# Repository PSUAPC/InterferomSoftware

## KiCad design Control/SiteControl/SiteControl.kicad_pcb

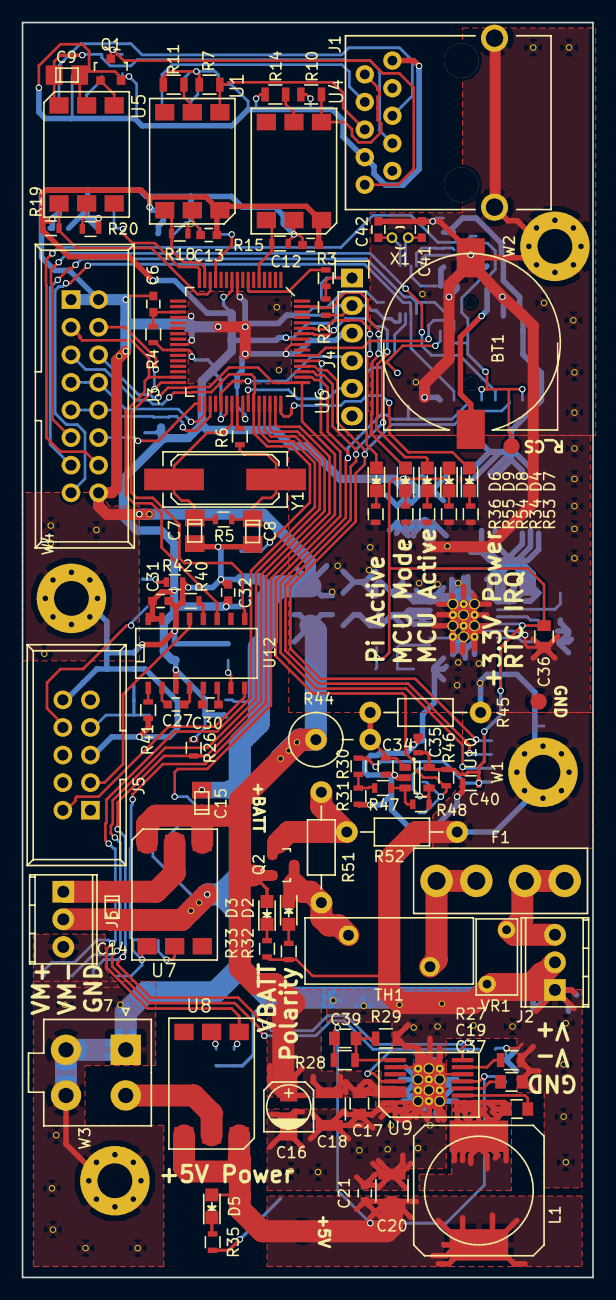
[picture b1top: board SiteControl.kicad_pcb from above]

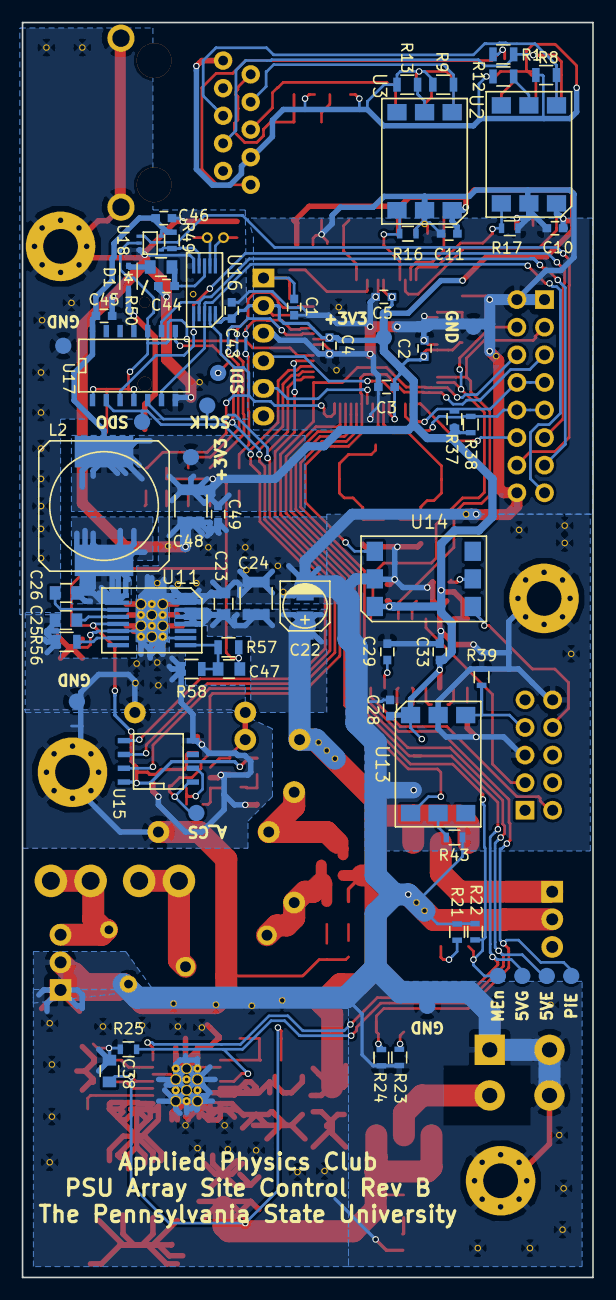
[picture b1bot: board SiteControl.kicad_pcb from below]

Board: 2 copper layers, 52.5 x 115.5 mm, 155 parts (55 on the bottom side), 103 nets.

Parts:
BT1: Keystone 1056; CoinCell_12.5mm
C1, C2, C3, C4, C5, C6: 100nF; C_0603
C7, C8: 30-36pF; TantalC_SizeR_EIA-2012
C9: 0.1uF; TantalC_SizeR_EIA-2012
C10, C11, C12, C13, C21, C27, C28, C29, C30, C31, C32, C33, C43, C44, C45, C46, C49: 0.1uF; C_0603
C14: 0.47uF; TantalC_SizeR_EIA-2012
C15: 22uF; TantalC_SizeR_EIA-2012
C16, C22: 47uF; c_elec_4x5.8
C17, C23: 1uF; C_0805
C18: 22uF; C_1210
C19, C25: 2.2uF; C_0805
C20: 47uF; C_1210
C24: 4.7uF; C_1210
C26, C37: 0.47uF; C_0805
C34, C35, C40: 0.1uF; R_0603
C36, C38: 4.7uF; C_0805
C39: 33pF; C_0805
C41: 8pF; C_0603
C42: 10pF; C_0603
C47: 18pF/25V; C_0805
C48: 100uF; C_1210
D1: CUS520,H3F; SOD-323
D2: Reverse Polarity Error; LED_0805
D3: BATT Power; LED_0805
D4: 3V3 Power; LED_0805
D5: 5V Power; LED_0805
D6: RPi VSENSE; LED_0805
D7: RTC_MFP; LED_0805
D8: MCU Active; LED_0805
D9: MCU Mode; LED_0805
F1: BK-6013; Mini-Blade_Fuse
J1: RJ50; RJ50_RJE051AA1310
J2, J6: CONN_01X03; TerminalBlock_Pheonix_MPT-2.54mm_3pol
J3: IDC_16Pin_Polarized; IDC_Header_Straight_16pins
J4: CONN_01X06; Pin_Header_Straight_1x06
J5: IDC-10_Polarized; IDC_Header_Straight_10pins
J7: Molex Minifit-JR 4.2mm; Molex_MiniFit-JR-5556-04A_2x02x4.20mm_Straight
L1, L2: 22uH; SELF-WE-PD-XXL
Q1: BC817-40; SOT-23
Q2: SI2323DDS-T1-GE3; SOT-23
R1, R7, R8, R9, R10: 10K; R_0805
R2, R22, R24, R25, R26: 10K; R_0603
R3: 100R; R_0603
R4: 10R; R_0603
R5, R39: R; R_0603
R6, R41: 0R; R_0603
R11, R12, R13, R14: 100R; R_0805
R15, R16, R17, R18, R19, R40, R46: 1K; R_0603
R20, R21, R23, R42, R43: 450R; R_0603
R27, R56: 205K; R_0805
R28, R57: 1M; R_0805
R29: 255K; R_0805
R30: 1M; R_0603
R31: 41K; R_0603
R32: 3K6; R_0603
R33: 5K6; R_0603
R34, R36, R53, R54, R55: 750R; R_0603
R35: 1K6; R_0603
R37, R38: 1K5; R_0603
R44: 1M; Resistor_Vertical_RM5mm
R45: 20K; Resistor_Horizontal_RM10mm
R47: 16K; R_0603
R48: 39K; R_0603
R49: 3k; R_0603
R50: 1R; C_0805
R51: 1M; Resistor_Horizontal_RM10mm
R52: 1M8; Resistor_Horizontal_RM10mm
R58: 442K; R_0805
TH1: SL15 60004; RV_Disc_D15.5_W6.1_P7.5
U1, U2, U3, U4, U5, U13, U14: Opto_H11L1M; H11L1M
U6: PIC16LF1947; PIC16_TDQFP64_pcb
U7, U8: SS_Relay_VO14642AT
U9, U11: LM43602; TI_HTSSOP-PWP-16
U10: LMV611; SOT-23-5
U12: ICL3221; SO-16-N
U15: 12-Bit SPI ADC; SOIC-8-N
U16: MCP7952; MSOP-10
U17: 74HCT125D,653; SOIC-14_N
U18: SN74AUP1T87_Schmitt_XNOR; SOT-353
VR1: MOV-07D270K; RV_Disc_D7_W3.8_P5
W1, W2, W3, W4: TEST_1P; MountingHole_3.2mm_M3_Pad_Via
X1: CFS-20632768EZBB_32.768kHz; Crystal_Round_Vertical_2mm
Y1: 4MHz; Q_49U3HMS

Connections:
+3.3VP: C44.1, R50.2, U16.3
+3V3: C2.1, C3.1, C4.1, C5.1, C10.1, C11.1, C12.1, C13.1, C28.1, C31.1, C32.1, C33.1, C35.1, C36.2, C40.1, C43.1, C45.1, C46.1, C47.2, C48.1, C49.1, D4.2, J4.2, L2.2, R2.2, R4.1, R19.2, R26.2, R30.1, R37.2, R38.2, R46.1, R49.1, R57.1, U1.6, U2.6, U3.6, U4.6, U6.10, U6.26, U6.38, U6.57, U10.5, U11.5, U12.3, U12.15, U12.16, U13.6, U14.6, U15.8, U16.10, U17.14, U18.5
+5V: C20.1, C21.1, C38.2, C39.2, D5.2, L1.2, R28.1, U8.4, U8.6, U9.5
+BATT: C15.1, C16.1, C17.2, C18.2, C22.1, C23.2, C24.2, D3.2, Q2.2, R44.1, U7.4, U7.6, U9.13, U9.14, U11.12, U11.13, U11.14
ADC_nCS: R46.2, U6.53, U15.1
CLKIN: C7.1, R5.1, U6.39, Y1.2
CLKOUT: R6.2, U6.40
CMOS_CTS: J3.5, U6.43, U14.4
CMOS_RTS: J3.6, U6.49, U13.1
CMOS_RX: J3.4, U6.32, U12.9
CMOS_TX: J3.3, U6.31, U12.11
GND: BT1.2, C1.2, C2.2, C3.2, C4.2, C5.2, C6.2, C7.2, C8.2, C10.2, C11.2, C12.2, C13.2, C14.2, C15.2, C16.2, C17.1, C18.1, C19.1, C20.2, C21.2, C22.2, C23.1, C24.1, C25.1, C28.2, C29.2, C31.2, C32.2, C33.2, C34.2, C35.2, C36.1, C38.1, C40.2, C41.2, C42.2, C43.2, C44.2, C45.2, C46.2, C48.2, C49.2, J1.11, J2.1, J2.2, J3.1, J3.2, J3.16, J4.3, J5.5, J5.10, J6.2, J6.3, J7.1, J7.3, J7.4, R15.1, R16.1, R17.1, R18.1, R20.1, R21.1, R22.1, R23.1, R24.1, R25.1, R27.1, R29.2, R31.2, R32.2, R33.2, R34.2, R35.2, R36.2, R39.2, R40.2, R41.2, R42.1, R43.2, R45.2, R52.2, R53.2, R54.2, R55.2, R56.1, R58.2, U1.5, U2.5, U3.5, U4.5, U6.9, U6.20, U6.25, U6.41, U6.56, U9.6, U9.10, U9.15, U9.16, U9.17, U10.2, U11.6, U11.10, U11.15, U11.16, U11.17, U12.14, U13.5, U14.5, U15.4, U16.5, U17.7, U18.3, VR1.2, W1.1, W2.1, W3.1, W4.1
I1: D2.1, Q2.3, R51.1, TH1.1
INV_Data_Safe: R15.2, U4.4, U6.5
INV_LCD_Data: J1.9, R10.1, U4.1
INV_LCD_GND: C9.2, J1.3, J1.10, Q1.2, R7.2, R8.2, R9.2, R10.2, R11.2, R12.2, R13.2, R14.2, U5.5
INV_LED_OverTemp: J1.6, R8.1, U2.1
INV_LED_Overload: J1.7, R9.1, U3.1
INV_LED_PowerOn: J1.5, R7.1, U1.1
INV_Overload_Safe: R16.2, U3.4, U6.13
INV_Power_Safe: R17.2, U2.4, U6.16
INV_TOGGLE: J1.1, Q1.3, R1.2
INV_Temp_Safe: R18.2, U1.4, U6.15
INV_Toggle_Safe: R19.1, U5.1, U6.14
INV_VCC: C9.1, J1.4, R1.1, U5.6
MCLR: C1.1, J4.1, R2.1, R3.2
MCU_Active: D8.2, U6.58
MCU_Mode: D9.2, U6.63
MODEM_CTS: J5.8, U14.1
MODEM_RTS: J5.7, R39.1, U13.4
Modem_En: R22.2, U6.47, U7.1
unnamed: BT1.1, D1.2
unnamed: C6.1, R4.2, U6.19
unnamed: C8.1, R5.2, R6.1, Y1.1
unnamed: C14.1, J6.1, U7.5
unnamed: C19.2, U9.4
unnamed: C25.2, U11.4
unnamed: C26.1, U11.3
unnamed: C26.2, L2.1, U11.1, U11.2
unnamed: C27.1, U12.2
unnamed: C27.2, U12.4
unnamed: C29.1, U12.7
unnamed: C30.1, U12.5
unnamed: C30.2, U12.6
unnamed: C34.1, R44.2, R45.1, U10.1
unnamed: C37.1, U9.3
unnamed: C37.2, L1.1, U9.1, U9.2
unnamed: C39.1, R28.2, R29.1, U9.9
unnamed: C41.1, U16.2, X1.2
unnamed: C42.1, U16.1, X1.1
unnamed: C47.1, R57.2, R58.1, U11.9
unnamed: D1.1, R50.1
unnamed: D2.2, R32.1
unnamed: D3.1, R33.1
unnamed: D4.1, R34.1
unnamed: D5.1, R35.1
unnamed: D6.1, R36.1
unnamed: D7.1, R53.1
unnamed: D8.1, R54.1
unnamed: D9.1, R55.1
unnamed: F1.1, J2.3, VR1.1
unnamed: F1.2, TH1.2
unnamed: J7.2, U8.5
unnamed: Q1.1, U5.4
unnamed: Q2.1, R51.2, R52.1
unnamed: R3.1, U6.7
unnamed: R11.1, U1.2
unnamed: R12.1, U2.2
unnamed: R13.1, U3.2
unnamed: R14.1, U4.2
unnamed: R20.2, U5.2
unnamed: R21.2, U7.2
unnamed: R23.2, U8.2
unnamed: R27.2, U9.7
unnamed: R30.2, R31.1, R47.2
unnamed: R40.1, U12.12
unnamed: R41.1, U12.1
unnamed: R42.2, U14.2
unnamed: R43.1, U13.2
unnamed: R47.1, R48.2, U10.3
unnamed: R48.1, U10.4, U15.2
unnamed: R56.2, U11.7
PGEC: J4.5, U6.42
PGED: J4.4, U6.37
PI_RTC_nCS: J3.14, U18.1
PI_SCLK: J3.15, U16.8, U17.6
PI_SDI: J3.13, U16.7, U17.9
PI_SDO: J3.11, U16.6, U17.3
PiSCL: J3.7, J3.8, R37.1, U6.34
PiSDA: J3.9, J3.10, R38.1, U6.35
Pi_Sense: D6.2, U6.59
Pi_VSense: J3.12, U6.33
RPi_5V_En: R25.2, U6.45, U9.12
RPi_5V_PGood: R26.1, U6.46, U9.8
RPi_En: R24.2, U6.44, U8.1
RS232_RX: J5.2, U12.8
RS232_TX: J5.3, U12.13
RTC_MFP: D7.2, U6.48, U16.9
RTC_nCS: U6.54, U17.1, U17.4, U17.10, U18.2
SCLK: U6.50, U15.7, U17.5
SDI: U6.51, U15.6, U17.8
SDO: U6.52, U15.5, U17.2
nCS: R49.2, U16.4, U18.4

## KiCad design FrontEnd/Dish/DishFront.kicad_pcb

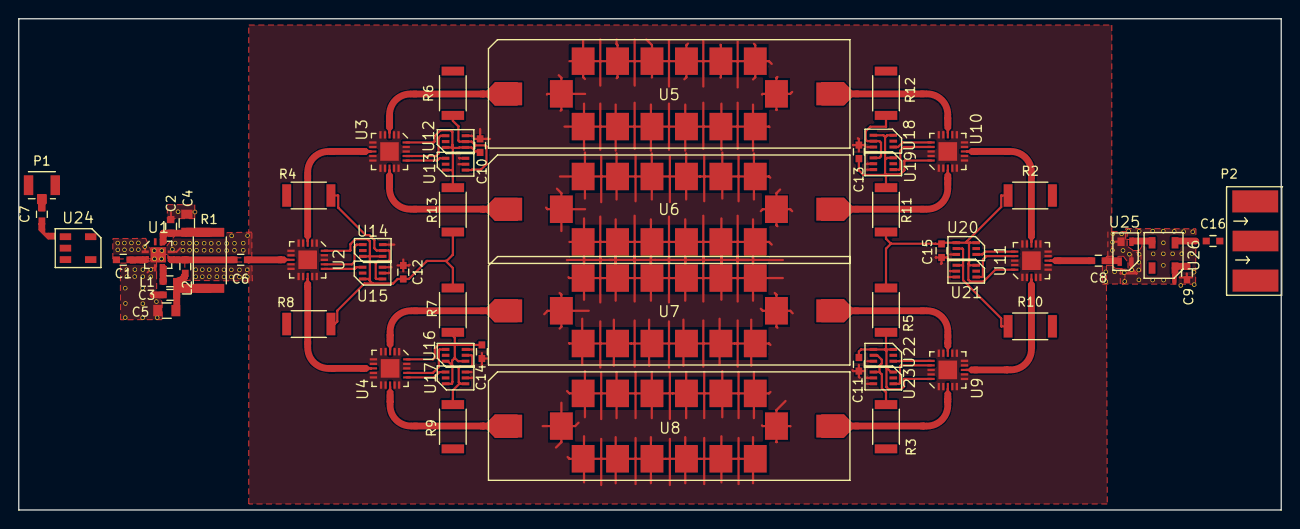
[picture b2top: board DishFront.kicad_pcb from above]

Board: 2 copper layers, 139.7 x 54.4 mm, 59 parts (0 on the bottom side), 42 nets.

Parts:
C1, C2, C3, C6, C7, C8, C16: 100pF; C_0603
C4, C5: 1uF; C_0805
C9, C10, C11, C12, C13, C14, C15: 0.1uF; C_0603
L1: 36nH; C_0603
L2: 47nH; C_0603
P1: BNC; UMCC_PCB
P2: BNC; SMA_EDGE
R1: 0R; R_2512
R2, R3, R4, R5, R6, R7, R8, R9, R10, R11, R12, R13: 0R; R_2010
U1: PMA-545G1_Amp; MC_DQ849
U2, U3, U4, U9, U10, U11: HSWA2-30DR_switch; MC_DG983-1
U5, U6, U7, U8: MC_HQ1157_Bandpass; MC_HQ1157
U12, U13, U14, U15, U16, U17, U18, U19, U20, U21, U22, U23: SN74AUP1T86_Schmitt_XOR; TI_DCK
U24: MC_DBTC-17-5_Coupler; MC_AT790-1
U25: PSA4-5043_Amp; MC_MMM1362
U26: MC_TCBT-2R5G_BiasT; MC_GU1604

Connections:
+3V3: C10.1, C11.1, C12.1, C13.1, C14.1, C15.1, R2.1, R2.2, R5.1, R5.2, R7.1, R7.2, R8.1, R8.2, R11.1, R11.2, R13.1, R13.2, U2.20, U3.20, U4.20, U9.20, U10.20, U11.20, U12.1, U12.6, U13.6, U14.1, U14.6, U15.6, U16.1, U16.6, U17.6, U18.1, U18.6, U19.6, U20.1, U20.6, U21.6, U22.1, U22.6, U23.6
+5V: C3.1, C5.1, C9.2, L1.1, L2.1, R1.2, U26.1
AMP1_Out: C6.1, U2.8
AMP2_In: C8.2, U11.8
GND: C2.2, C3.2, C4.2, C5.2, C9.1, C10.2, C11.2, C12.2, C13.2, C14.2, C15.2, P1.2, P2.2, U1.9, U2.1, U2.2, U2.4, U2.5, U2.6, U2.7, U2.9, U2.10, U2.11, U2.12, U2.14, U2.15, U2.18, U2.19, U2.21, U3.1, U3.2, U3.4, U3.5, U3.6, U3.7, U3.9, U3.10, U3.11, U3.12, U3.14, U3.15, U3.18, U3.19, U3.21, U4.1, U4.2, U4.4, U4.5, U4.6, U4.7, U4.9, U4.10, U4.11, U4.12, U4.14, U4.15, U4.18, U4.19, U4.21, U5.2, U5.3, U5.4, U5.5, U5.6, U5.7, U5.9, U5.10, U5.11, U5.12, U5.13, U5.14, U6.2, U6.3, U6.4, U6.5, U6.6, U6.7, U6.9, U6.10, U6.11, U6.12, U6.13, U6.14, U7.2, U7.3, U7.4, U7.5, U7.6, U7.7, U7.9, U7.10, U7.11, U7.12, U7.13, U7.14, U8.2, U8.3, U8.4, U8.5, U8.6, U8.7, U8.9, U8.10, U8.11, U8.12, U8.13, U8.14, U9.1, U9.2, U9.4, U9.5, U9.6, U9.7, U9.9, U9.10, U9.11, U9.12, U9.14, U9.15, U9.18, U9.19, U9.21, U10.1, U10.2, U10.4, U10.5, U10.6, U10.7, U10.9, U10.10, U10.11, U10.12, U10.14, U10.15, U10.18, U10.19, U10.21, U11.1, U11.2, U11.4, U11.5, U11.6, U11.7, U11.9, U11.10, U11.11, U11.12, U11.14, U11.15, U11.18, U11.19, U11.21, U12.3, U13.2, U13.3, U14.3, U15.2, U15.3, U16.3, U17.2, U17.3, U18.3, U19.2, U19.3, U20.3, U21.2, U21.3, U22.3, U23.2, U23.3, U24.2, U25.2, U25.4
unnamed: C1.1, U1.2
unnamed: C2.1, C4.1, R1.1, U1.7
unnamed: C6.2, L2.2, U1.5
unnamed: C7.1, U24.1
unnamed: C7.2, P1.1
unnamed: C8.1, U25.3
unnamed: C16.1, U26.4
unnamed: C16.2, P2.1
unnamed: L1.2, U1.4
unnamed: U1.1, U1.3, U1.6, U1.8
unnamed: U2.3, U3.8
unnamed: U2.13, U4.8
unnamed: U3.3, U5.1
unnamed: U3.13, U6.1
unnamed: U4.3, U7.1
unnamed: U4.13, U8.1
unnamed: U7.8, U9.13
unnamed: U8.8, U9.3
unnamed: U6.8, U10.3
unnamed: U10.8, U11.13
unnamed: U5.8, U10.13
unnamed: U9.8, U11.3
unnamed: U25.1, U26.3
S1C1: U2.17, U14.4
S1C2: U2.16, U15.4
S1_CTRL: R4.1, R4.2, R10.1, R10.2, U14.2, U15.1, U20.2, U21.1
S2C1: U3.17, U12.4
S2C2: U3.16, U13.4
S2CTRL: R3.1, R3.2, R6.1, R6.2, R9.1, R9.2, R12.1, R12.2, U12.2, U13.1, U16.2, U17.1, U18.2, U19.1, U22.2, U23.1
S3C1: U4.17, U16.4
S3C2: U4.16, U17.4
S4C1: U9.16, U22.4
S4C2: U9.17, U23.4
S5C1: U10.16, U18.4
S5C2: U10.17, U19.4
S6C1: U11.16, U20.4
S6C2: U11.17, U21.4

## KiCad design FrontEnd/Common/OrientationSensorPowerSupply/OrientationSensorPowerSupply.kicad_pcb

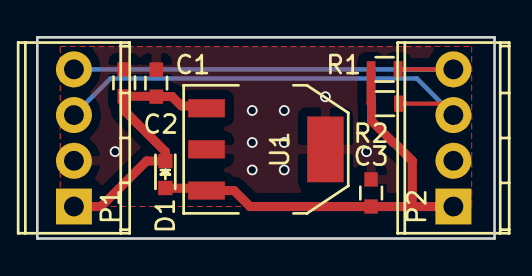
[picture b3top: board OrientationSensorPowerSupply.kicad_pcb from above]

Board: 2 copper layers, 25.4 x 11.2 mm, 9 parts (0 on the bottom side), 5 nets.

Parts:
C1, C3: 1uF; C_0603
C2: 10uF; C_0603
D1: D; LED_0603
P1, P2: CONN_01X04; TerminalBlock_Pheonix_MPT-2.54mm_4pol
R1: 3.3K; R_0603
R2: 3.3k; R_0603
U1: 7805; SOT-223

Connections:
GND: C1.2, C2.2, C3.2, P1.2, P2.2, U1.GND
unnamed: C1.1, C2.1, D1.1, P1.1, U1.VI
unnamed: C3.1, D1.2, P2.1, R1.1, R2.1, U1.VO
SCL: P1.4, P2.4, R1.2
SDA: P1.3, P2.3, R2.2

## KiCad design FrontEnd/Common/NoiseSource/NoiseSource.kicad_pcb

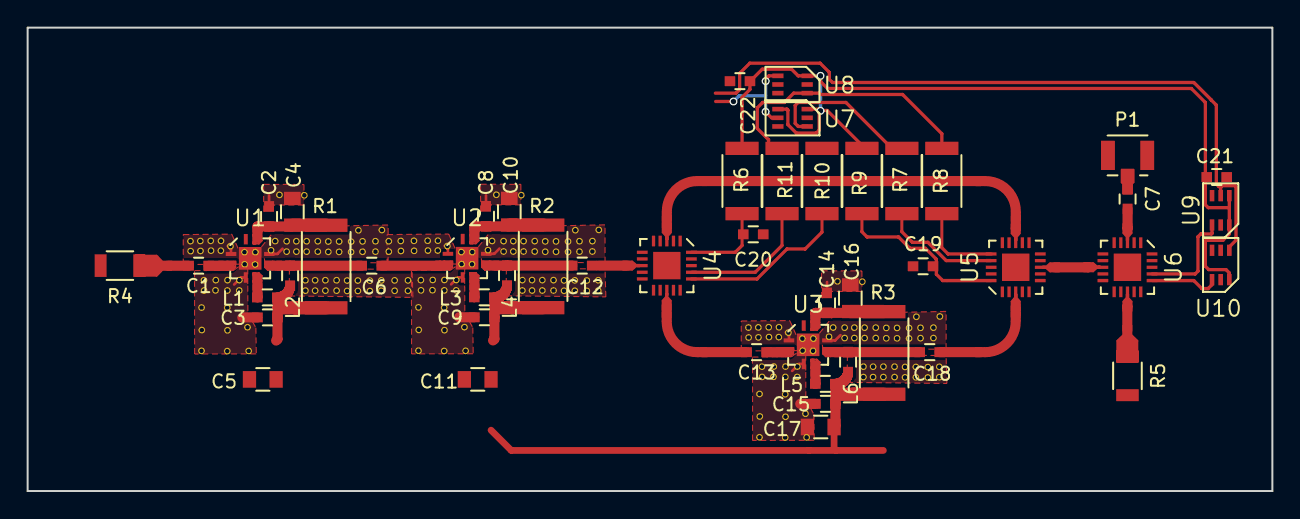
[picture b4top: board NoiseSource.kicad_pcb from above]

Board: 2 copper layers, 93.5 x 34.8 mm, 50 parts (0 on the bottom side), 34 nets.

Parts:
C1, C2, C3, C6, C7, C8, C9, C12, C13, C14, C15, C18: 100pF; C_0603
C4, C5, C10, C11, C16, C17: 1uF; C_0805
C19, C20, C21, C22: 0.1Uf; C_0603
L1, L3, L5: 36nH; C_0603
L2, L4, L6: 47nH; C_0603
P1: BNC; UMCC_PCB
R1, R2, R3: 0R; R_2512
R4, R5: 50R; R_1206
R6, R7, R8, R9, R10, R11: 0R; R_2010
U1, U2, U3: PMA-545G1_Amp; MC_DQ849
U4, U5, U6: HSWA2-30DR_switch; MC_DG983-1
U7, U8, U9, U10: SN74AUP1T86_Schmitt_XOR; TI_DCK

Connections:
+3V3: C21.2, C22.2, R6.2, R9.2, U7.1, U7.6, U8.6, U9.1, U9.6, U10.6
+5V: C3.1, C5.1, C9.1, C11.1, C15.1, C17.1, L1.1, L2.1, L3.1, L4.1, L5.1, L6.1, R1.2, R2.2, R3.2
CTRL1: R7.2, R10.2, U7.4
CTRL2: R8.2, R11.2, U8.4
GND: C2.2, C3.2, C4.2, C5.2, C8.2, C9.2, C10.2, C11.2, C14.2, C15.2, C16.2, C17.2, C19.1, C20.1, C21.1, C22.1, P1.2, R4.2, R5.2, U1.9, U2.9, U3.9, U4.1, U4.2, U4.4, U4.5, U4.6, U4.7, U4.8, U4.9, U4.10, U4.11, U4.12, U4.14, U4.15, U4.18, U4.19, U4.21, U5.1, U5.2, U5.4, U5.5, U5.6, U5.7, U5.8, U5.9, U5.10, U5.11, U5.12, U5.14, U5.15, U5.18, U5.19, U5.21, U6.1, U6.2, U6.4, U6.5, U6.6, U6.7, U6.8, U6.9, U6.10, U6.11, U6.12, U6.14, U6.15, U6.21, U7.3, U8.2, U8.3, U9.3, U10.2, U10.3
unnamed: C1.1, U1.2
unnamed: C1.2, R4.1
unnamed: C2.1, C4.1, R1.1, U1.7
unnamed: C6.1, U2.2
unnamed: C6.2, L2.2, U1.5
unnamed: C7.1, P1.1
unnamed: C7.2, U6.3
unnamed: C8.1, C10.1, R2.1, U2.7
unnamed: C12.2, L4.2, U2.5
unnamed: C13.1, U3.2
unnamed: C13.2, U4.13
unnamed: C14.1, C16.1, R3.1, U3.7
unnamed: C18.1, U5.3
unnamed: C18.2, L6.2, U3.5
unnamed: L1.2, U1.4
unnamed: L3.2, U2.4
unnamed: L5.2, U3.4
unnamed: R5.1, U6.13
unnamed: U1.1, U1.3, U1.6, U1.8
unnamed: U2.1, U2.3, U2.6, U2.8
unnamed: U3.1, U3.3, U3.6, U3.8
unnamed: U4.3, U5.13
ShuntCTRL1: U6.17, U9.4
ShuntCTRL2: U6.16, U10.4
ShuntSel: U9.2, U10.1
SolarSel: U7.2, U8.1
TCTRL1: R7.1, R10.1, U4.16, U5.17
TCTRL2: R8.1, R11.1, U4.17, U5.16
TVDD: C19.2, C20.2, R6.1, R9.1, U4.20, U5.20

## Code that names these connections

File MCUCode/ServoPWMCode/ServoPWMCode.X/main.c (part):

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// Use project enums instead of #define for ON and OFF.

// CONFIG1
#pragma config FOSC = INTOSC    // Oscillator Selection Bits (INTOSC oscillator: I/O function on CLKIN pin)
#pragma config WDTE = OFF       // Watchdog Timer Enable (WDT disabled)
#pragma config PWRTE = ON      // Power-up Timer Enable (PWRT disabled)
#pragma config MCLRE = ON       // MCLR Pin Function Select (MCLR/VPP pin function is MCLR)
#pragma config CP = OFF         // Flash Program Memory Code Protection (Program memory code protection is disabled)
#pragma config BOREN = ON       // Brown-out Reset Enable (Brown-out Reset enabled)
#pragma config CLKOUTEN = OFF    // Clock Out Enable (CLKOUT function is enabled on the CLKOUT pin)
#pragma config IESO = ON        // Internal/External Switchover Mode (Internal/External Switchover Mode is enabled)
#pragma config FCMEN = ON       // Fail-Safe Clock Monitor Enable (Fail-Safe Clock Monitor is enabled)

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
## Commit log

2015-05-04 implemented some basic makefiles for the server and RPi
2015-05-04 added READMEs
2015-05-04 basic RPi Daemon code
2015-05-12 successfully implemented basic comm daemon with a restart daemon
2015-05-19 basic wireless comm API
2015-05-23 added libraries and some barebones code
2015-05-30 implemented some UART functionality for wireless modem
2015-08-20 added init script for comm runner daemon
2015-08-24 added posix and tcp test code
2015-08-25 got server-client working, with timeout accept
2015-08-25 successful client and server connection - disconnection behavior
2015-08-26 got the chat client to work!
2015-10-25 basic VHDL Code added
2015-10-25 added integrator CPLD code
2015-10-25 removed some unneeded files
2016-02-21 added parallel support for the w5100 library
2016-04-23 added PCB libs
2016-04-27 more library parts added
2016-05-07 [Added] Test code for the RPi to communicate with the I2C position sensors
2016-05-07 [Added] Readme to MCUI2CTest directory
2016-05-07 [Modified] MCUI2CTest directory structure
2016-05-10 [Fixed] I2COrient3 now correctly initializes and reads the accelerometer
2016-05-10 [Added] Magnetometer functionality to I2COrient3 program
2016-05-10 [Fixed] Magnetometer temperature and field reading levels in I2COrient3 program
2016-06-21 [Added] Servo control MCU code
2016-06-21 [Added] MCUCommTest; [Added] better gitignore
2016-06-21 [Removed] MCU Artifacts
2016-06-22 [Modified] gitignores; [Modified] Dir Structure for test program; [Added] NCurses Terminal Test
2016-06-22 [Added] Generic Shell Framework for ncurses terminal test
2016-06-22 [Added] TCPConnect Hook; [Fixed] History display and history scroll up bug
2016-06-24 [Added] IP Connect command; [Added] serial device command
2016-06-24 [Added] optarg support for shell commands
2016-06-25 [Added] Man command framework; [Added] newline support in printToStdout string
2016-06-25 [Added] Echo command; [Added] Run command to run commands from a file
2016-06-25 [Fixed] A bug with resetting optarg, turns out it uses global variables which must be reset
2016-06-25 [Modified] consolidated the tcp commands into one with arguments
2016-06-26 [Added] TTY and UDP variables for connection
2016-06-26 Initial Branch Commit
2016-06-26 [Migrated] Ncurses code to NWindow
2016-06-26 [Migrated] Fully migrated ncurses control to the NWindow class, and added NTerminal as a widget
2016-06-27 [Added] sizers
2016-06-27 [Added] Panel Widget to handle boarders
2016-06-28 [Added] Panel boarders and selection feedback; [Fixed] resize updating, sizers now update
2016-06-28 [Fixed] a stupid typo
2016-06-28 [Added] Tab widget display functionality
2016-06-28 [WIP] Focus control between widget
2016-06-28 [WIP] same level tabs work
2016-06-28 [FIXED] up focus direction on main NWindow
2016-06-30 [Fixed] Blank screen when adding another widget. Must assign the mutex to the window at the very begining
2016-07-02 [Added] Shell back to the terminal, and fixed the terminal to work with a border and a vertical cutoff
2016-07-02 [Merged] Widget Dev into master
2016-07-02 [Cleaned] some of the code from testing the widgets
2016-07-02 [Added] a hex display widget that can display a hex stream; [Added] widget focus ability, which allows for only the focused widget to capture input; [Fixed] the cursor position showing in a strange l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
2016-07-02 [Fixed] Cosmetic change with the hex viewer; [Fixed] bug with hex viewer truncating lines if the entire stream fits on the screen
2016-07-02 [Added] Serial tty connection functionality, and verified that it is working properly
2016-07-02 [Added] a send sub-command to tty (will add to tcp soon) which takes a hex string as an argument
2016-07-03 [Added] byte stream send ability for tty and tcp
2016-07-04 [Added] Message queues for TCP and TTY threads - implemented TCP send and recv with the queue
2016-07-04 [Added] TTY send and recv ability with thread and message queues
2016-07-04 [Added] FIFO which is made Threadsafe for the TTY inbox stream
2016-07-10 [Copied] NCurses code into MCU Comm Test; [Added] Packet Inspector to Hex Viewer in MCU Comm Test
2016-07-11 [Fixed] Bug with getopt. getopt returns and int not a char
2016-07-11 [Added] Front End MCU Code
2016-07-11 [Fixed] FIFO UART functionality bugs; [Added] Checksum verification on UART FIFO packets
2016-07-12 [Added] voltatile and eeprom register layout
2016-07-13 [Added] I2C routines, started working on Mag and Acc communication
2016-07-13 [WIP] Implementing state diagrams for MCU firmare
2016-07-15 [Added] UART packet sending
2016-08-08 [Added] All local working copies; [Changed] organization of files
2016-08-08 [Moved] Old files into old-file dir; [Added] Control system files and added old files
2016-08-09 [WIP] Converting the battery interceptor board to kicad - new KiCad board contains a high effciency buck converter... may be overkill
2016-08-09 [Changed] RPi buck converter circuit to be lower power (1.8A)
2016-08-10 [WIP] Completed prelimary circuit and layout of the base control board
2016-08-10 [Added] 3D models for parts on the base controller
2016-08-10 [Added] more 3D models for the base control board. Rearanged parts a bit to allow for better clearance as per the 3D models
2016-08-11 [Added] Mechanical drawings for control board mounting case
2016-08-11 [Added] Engineering notes to the system control schematics; [Added] drawing of system control enclosure layout, as well as a sketch of wiring between boards and knockouts for within the enclosure
2016-08-11 [Changed] Moved mounting holes on control board to positions aligned to 1/16 inch grid
2016-08-12 [Completed] Layout of controller board (passed DRC) - still needs silkscreen fix
2016-08-12 [Changed] Moved the silkscreen identifies as well as added relevant silkscreen text to the board - it should be good to submit to the fab
2016-08-16 [Added] working copies of MCU test code from the Raspberry Pi
2016-08-16 [Updated] Readme files
2016-08-29 [Added] Site control BOM
2016-08-30 [Added] Minicircuits footprints for KiCad
2016-08-30 [Added] More trace transitions for RF; [Added] Schematic / PCB block for the wideband amplifier
2016-08-30 [Added] Minicircuits footprint test project; [Modified] amplifier block to include stitching vias
2016-08-30 [Added] 3D models for minicircuits parts
2016-08-31 [Added] Noise source board (moved to kicad); [Added] basic representation of front ends to play around with positioning and engineering; [Fixed] an error with some of the minicircuit parts not having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
2016-08-31 [Removed] clutter text on amplifier block; [Added] basic project for the dish front-end
2016-09-01 [Added] TI schmitt XOR component; [WIP] Dish front end; [Added] More RF trace adapters
2016-09-01 [Fixed] 30mil RF Miter to maintain constant impedance; [Added] 30 mil 90-degree arc; [WIP] Dish front end
2016-09-01 [Fixed] Minicircuits Bias Tee pad numbering issue; [Added] SMA Edge mount part
2016-09-06 [Added] More parts
2016-09-28 [Added] more parts; [Updated] Site Control board schematic to Rev B; [WIP] Site Control board pcb layout for Rev B.
2016-09-28 [Added] indicator LEDs and a new 3V3 Buck Converter to Site Control Board
2016-09-29 [WIP] Preliminary routing and silkscreen placement for Rev B of Site Control Board Compelte
2016-09-29 [Added] More parts; [Completed] Site Control Rev B Layout
2016-09-30 [Added] Test Pads to Site Control Board; [Completed] Site contorl board DRC
2016-09-30 [Updated] RF Modem power port to include an additional ground wire; [Fixed] LM43602 footprint vias by increasing their drill size to 13mils
2016-10-10 [Fixed] Site Control Input Protection Circuit
2016-10-23 [Added] custom 0603 Resistor footprint
2016-11-11 [Added] minicircuits lib, was ignored by gitignore before
2017-03-01 [Added] more schematic symbols and footprints to the PCB lib
2017-03-02 [Added] 3D models for some PCB footprints
2017-03-03 [Added] More PCB components and more 3D modeles for them
2017-03-04 [Added] more PCB footprints and 3D models
2017-03-13 [Added] More PCB footprints / 3D models
2018-03-02 [Added] Z510 Processor
2018-03-02 [Fixed] Z510 mislabled pins
